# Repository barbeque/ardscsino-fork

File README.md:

## Current Status
Dirty ArdSCSIno II, V1 board works on at least one system using the BlueSCSI v1 USB firmware. Please refer to the table below for full testing.

| Platform          | Works?    | Comments |
|-------------------|-----------|----------|
| Macintosh LC | Yes | With termination power |

## Flashing
**Warning**: these instructions are a work in progress. Please report any hangups (that aren't related to crappy Blue Pills, see below) so we can fix this section.

I have used [the BlueSCSI Updater project](https://github.com/erichelgeson/BlueSCSI-Updater) to flash these, but you can also use the QMK Toolbox project which basically runs the same commands.

You will need an STLink-V2 programmer (eBay clones are fine) and at least four jumper wires. I recommend doing this before you solder the Blue Pill to the board.

 1. Wire up the STLink-V2, making sure to pay attention to where on the programmer each wire ends up.
 2. Set the BOOT0 jumper (_furthest_ from the Reset switch) to 1 and connect the STLink-V2 to your computer.
 3. Run the BlueSCSI Updater, and select option 2 to program a bare Blue Pill board. The STLink should flash and then state that things are all good.
 4. Do not hit Return yet!
 5. Unplug the STLink-V2 from both the Blue Pill and the computer. 
 6. Reset the BOOT0 jumper to 0. Set the BOOT1 jumper (_closest_ to the reset switch) to 1.
 7. Plug the Blue Pill into your computer through USB. Wait a couple seconds.
 8. Now you can hit Return and let the BlueSCSI Updater flash your Blue Pill.
 9. Unplug it, set the jumpers back to default, and enjoy your board.

For the boards without jumpers (i.e. the USB-C ones that I warn about lower down - go take a look) you can do the following steps instead:

 0. Do all the preceding steps from the regular Blue Pill.
 1. Hold the BOOT0 button on the Blue Pill while inserting the ST-Link into your computer. Keep holding it while you run the BlueSCSI Updater and write the bare firmware. Release the BOOT0 button and unplug it and the ST-Link once done.
 2. In stage two, plug the Blue Pill in via USB-C, start the firmware update process, and hit the nRST (reset) button on the top when the flasher is waiting for the device to appear. It should proceed.

## Bill of Materials (BOM)

| Position | Component              | Digi-Key part number | Comments                               |
|----------|------------------------|----------------------|----------------------------------------|
| C1 | 4.7µF through-hole capacitor | | |
| C2 | 0.1µF 0805 SMD ceramic capacitor | | |
| D1 | Optional activity LED, 3mm radial | | |
| J1 | 50-pin SCSI box header, male | 3M157291-ND | |
| J2 | 4-pin Berg floppy power, TE 171825-4 | A106197-ND | |
| J3 | micro SD card slot, Hirose DM3AT-SF-PEJM5 | HR1964CT-ND | |
| U2 | STM32 Blue Pill **C8T6** | | This should be sourced from AliExpress; see below for common problems. |
| R1 | 560Ω through-hole resistor | | |
| RN1, RN4 | 10-pin (9-way) bussed 220Ω resistor network | 4610X-1-221LF-ND | |
| RN2, RN3 | 10-pin (9-way) bussed 330Ω resistor network | 4610X-1-331LF-ND | |

## Common Blue Pill problems
Because the STM32 Blue Pill has been knocked off by a jillion different individuals, here are some of the problems I've encountered while trying to build these boards.

You might want to try the [Blue Pill Diagnostics project](https://mecrisp-stellaris-folkdoc.sourceforge.io/bluepill-diags-v1.640.html#diags-1-640). Again, it's a good idea to run this before you solder your microcontroller down. It really sucks to desolder it after! Ask me how I know.

### Surprise +5V pin
On many Blue Pills sold today, pin 40 is a "5V" pin. My board expects this pin to be ground. If you try to bring it up without modification, it will short the +5V power supply to ground and probably cause something unpleasant to happen.

The best thing to do here is to simply not solder this pin to the board: I do a 20-pin male header on one side and a 19-pin male header on the other side.

Please notice also that the LED pin on this board is changed from normal; BlueSCSI firmware will expect it at PC13 and this one is at PB2.

### Not enough flash
Make sure you are getting a STM32...C8T6 board. These have enough flash for the BlueSCSI firmware. Otherwise, you can get a mysterious `LIBUSB_ERROR_TIMEOUT` (C6T6) and nothing will work.

The Blue Pill Diagnostics should report that you have at least 64kB of regular flash and at least 64kB of "hidden" flash. A C6 has only 32kB.

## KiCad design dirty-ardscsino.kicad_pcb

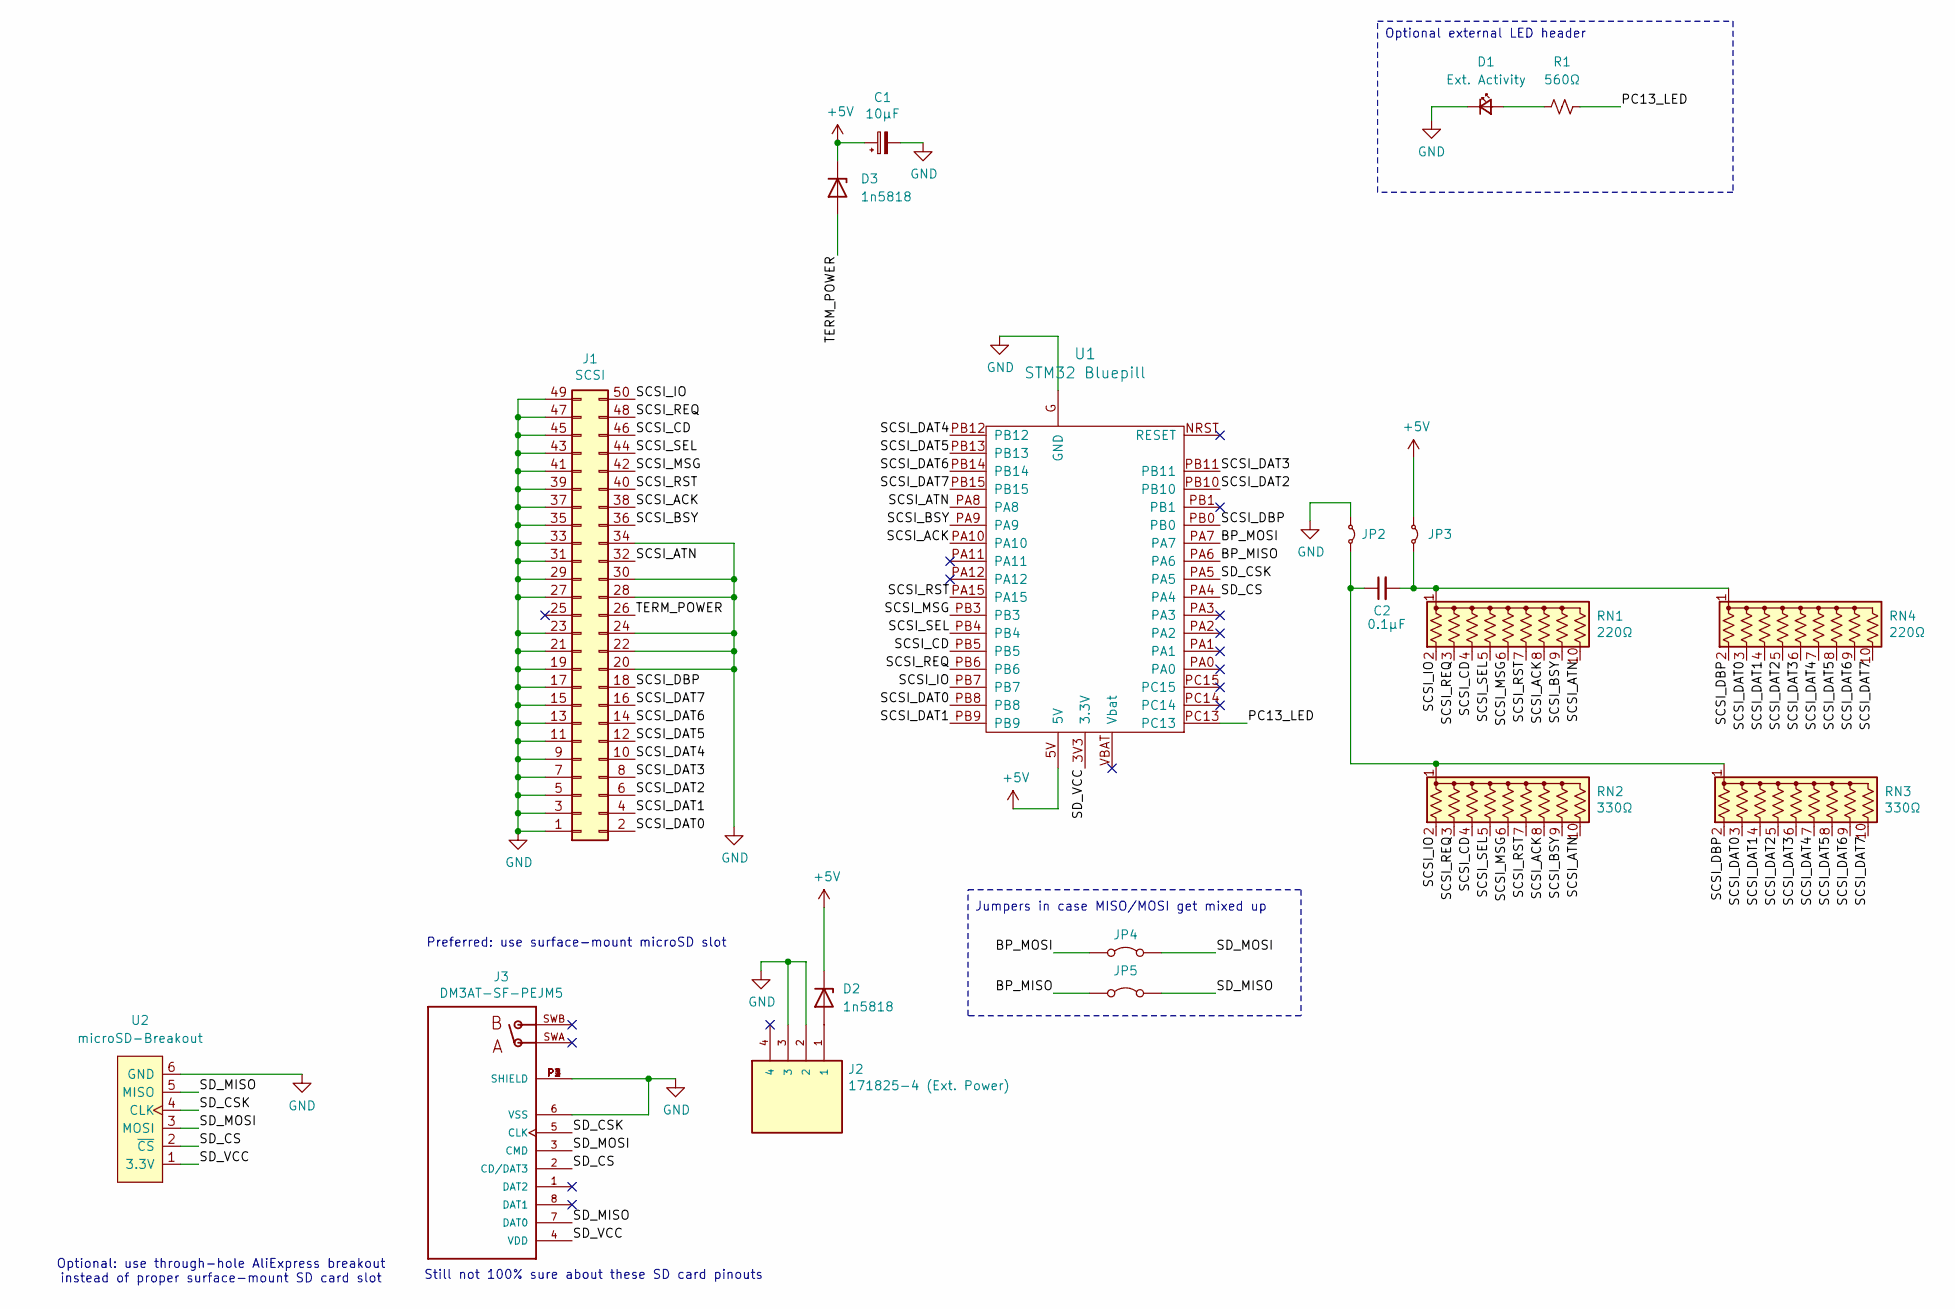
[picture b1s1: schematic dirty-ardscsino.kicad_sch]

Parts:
C1: 10µF; CP_Radial_D5.0mm_P2.00mm
C2: 0.1µF; C_0805_2012Metric_Pad1.18x1.45mm_HandSolder
D1: Ext. Activity; LED_D3.0mm
D2, D3: 1n5818; D_DO-41_SOD81_P7.62mm_Horizontal
J1: SCSI; PinHeader_2x25_P2.54mm_Horizontal; DigiKey 3M157291-ND
J2: 171825-4 (Ext. Power); TE_171825-4; DigiKey A106197-ND
J3: DM3AT-SF-PEJM5; HRS_DM3AT-SF-PEJM5; DigiKey HR1964CT-ND
JP2, JP3: Jumper_2_Small_Bridged; SolderJumper-2_P1.3mm_Bridged_RoundedPad1.0x1.5mm
JP4, JP5: Jumper_2_Bridged; SolderJumper-2_P1.3mm_Bridged_RoundedPad1.0x1.5mm
R1: 560Ω; R_Axial_DIN0207_L6.3mm_D2.5mm_P10.16mm_Horizontal
RN1, RN4: 220Ω; R_Array_SIP10; DigiKey 4610X-1-221LF-ND
RN2, RN3: 330Ω; R_Array_SIP10; DigiKey 4610X-1-331LF-ND
U1: STM32 Bluepill; blue_pill
U2: microSD-Breakout; microSD_AliExpress

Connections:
+5V: C1.1, D2.1 (K), D3.1 (K), JP3.1 (A), U1.5V
/BP_MISO: JP5.1 (A), U1.PA6
/BP_MOSI: JP4.1 (A), U1.PA7
/PC13_LED: R1.2, U1.PC13
/SCSI_ACK: J1.38, RN1.8 (R7), RN2.8 (R7), U1.PA10
/SCSI_ATN: J1.32, RN1.10 (R9), RN2.10 (R9), U1.PA8
/SCSI_BSY: J1.36, RN1.9 (R8), RN2.9 (R8), U1.PA9
/SCSI_CD: J1.46, RN1.4 (R3), RN2.4 (R3), U1.PB5
/SCSI_DAT0: J1.2, RN3.3 (R2), RN4.3 (R2), U1.PB8
/SCSI_DAT1: J1.4, RN3.4 (R3), RN4.4 (R3), U1.PB9
/SCSI_DAT2: J1.6, RN3.5 (R4), RN4.5 (R4), U1.PB10
/SCSI_DAT3: J1.8, RN3.6 (R5), RN4.6 (R5), U1.PB11
/SCSI_DAT4: J1.10, RN3.7 (R6), RN4.7 (R6), U1.PB12
/SCSI_DAT5: J1.12, RN3.8 (R7), RN4.8 (R7), U1.PB13
/SCSI_DAT6: J1.14, RN3.9 (R8), RN4.9 (R8), U1.PB14
/SCSI_DAT7: J1.16, RN3.10 (R9), RN4.10 (R9), U1.PB15
/SCSI_DBP: J1.18, RN3.2 (R1), RN4.2 (R1), U1.PB0
/SCSI_IO: J1.50, RN1.2 (R1), RN2.2 (R1), U1.PB7
/SCSI_MSG: J1.42, RN1.6 (R5), RN2.6 (R5), U1.PB3
/SCSI_REQ: J1.48, RN1.3 (R2), RN2.3 (R2), U1.PB6
/SCSI_RST: J1.40, RN1.7 (R6), RN2.7 (R6), U1.PA15
/SCSI_SEL: J1.44, RN1.5 (R4), RN2.5 (R4), U1.PB4
/SD_CS: J3.2 (CD/DAT3), U1.PA4, U2.2 (~CS)
/SD_CSK: J3.5 (CLK), U1.PA5, U2.4 (CLK)
/SD_MISO: J3.7 (DAT0), JP5.2 (B), U2.5 (MISO)
/SD_MOSI: J3.3 (CMD), JP4.2 (B), U2.3 (MOSI)
/SD_VCC: J3.4 (VDD), U1.3V3 (3.3V), U2.1 (3.3V)
/TERM_POWER: D3.2 (A), J1.26
GND: C1.2, D1.1 (K), J1.1, J1.3, J1.5, J1.7, J1.9, J1.11, J1.13, J1.15, J1.17, J1.19, J1.20, J1.21, J1.22, J1.23, J1.24, J1.27, J1.28, J1.29, J1.30, J1.31, J1.33, J1.34, J1.35, J1.37, J1.39, J1.41, J1.43, J1.45, J1.47, J1.49, J2.2, J2.3, J3.6 (VSS), J3.P1 (SHIELD), J3.P2 (SHIELD), J3.P3 (SHIELD), J3.P4 (SHIELD), JP2.1 (A), U1.G (GND), U2.6 (GND)
unnamed: D1.2 (A), R1.1
unnamed: D2.2 (A), J2.1
unnamed: C2.1, JP2.2 (B), RN2.1 (common), RN3.1 (common)
unnamed: C2.2, JP3.2 (B), RN1.1 (common), RN4.1 (common)

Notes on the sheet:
Preferred: use surface-mount microSD slot
Jumpers in case MISO/MOSI get mixed up
Optional: use through-hole AliExpress breakout instead of proper surface-mount SD card slot
Optional external LED header
Still not 100% sure about these SD card pinouts

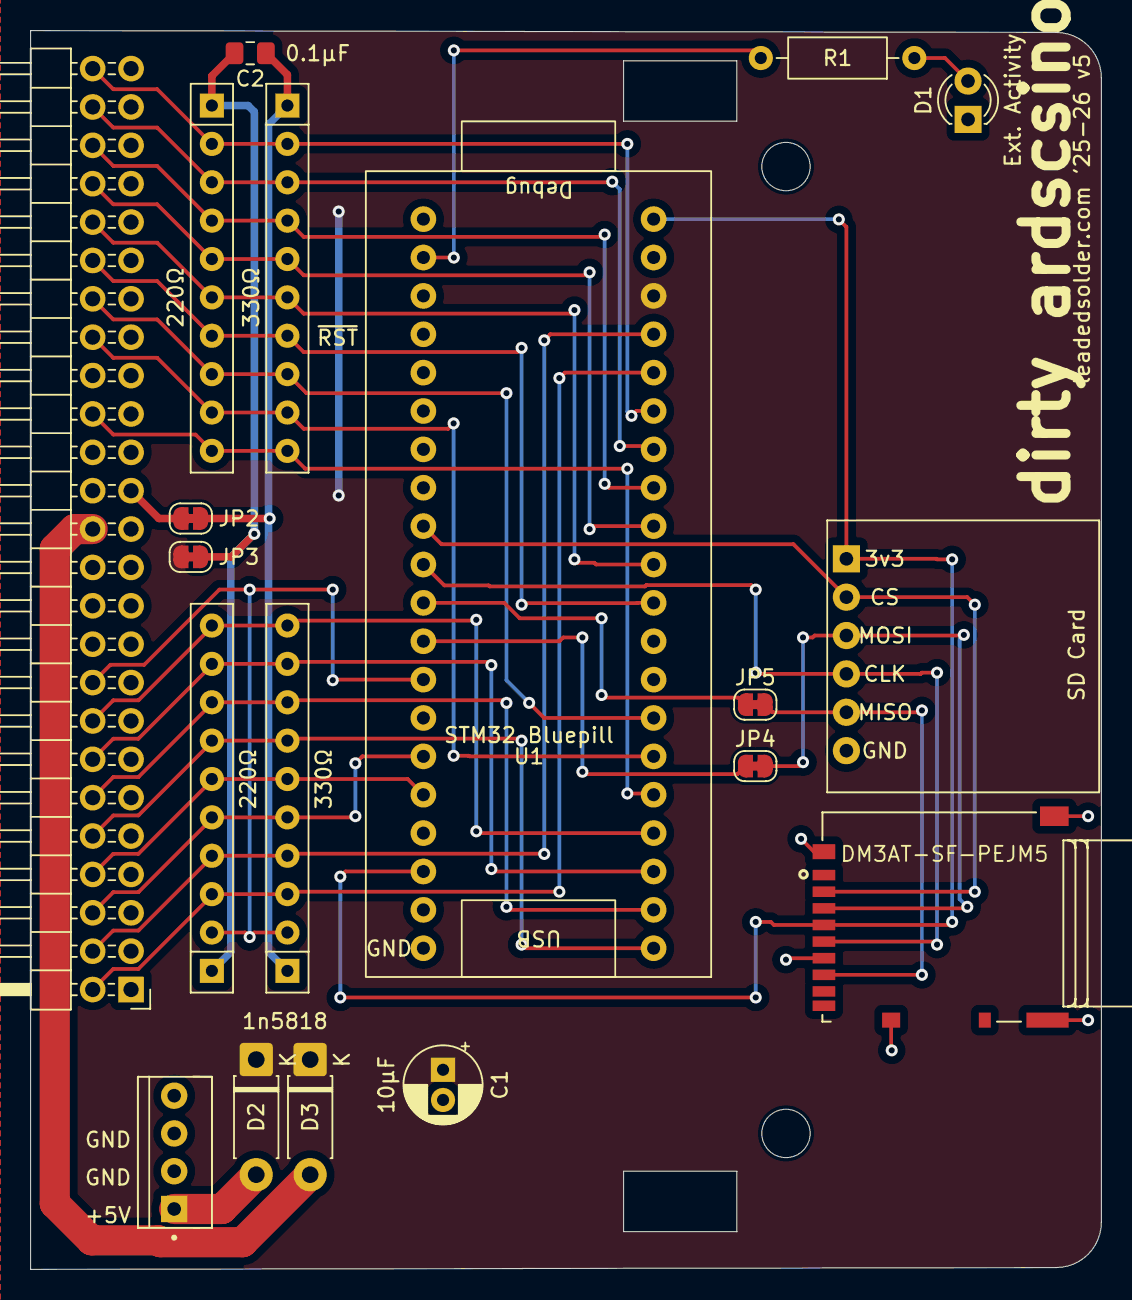
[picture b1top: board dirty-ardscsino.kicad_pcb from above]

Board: 2 copper layers, 70.9 x 82.0 mm, 19 parts (0 on the bottom side), 33 nets.

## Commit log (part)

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2021-02-18 Diagrams and footprints
2021-02-18 Termination resistors
2021-02-19 Layout except for SD card
2021-02-19 Add OSHW
2021-02-19 Passed DRC
2021-02-19 Gerber v0.1 test
2021-02-19 Clean up notes
2021-02-19 Add shore power switch and decoupling
2021-02-19 Clean up silks
2021-02-19 Add a smaller bypass to the termination grid as well
2021-02-19 Missed this before
2021-02-19 Move the cap so I don't hit it with USB
2021-02-23 Add 180-degree floppy power conn
2021-02-23 Add DigiKey BOM tags
2021-02-23 Fix the footprint tab AGAIN
2023-05-12 Good looking board layout
2024-04-09 KiCad upgrade
2024-04-09 Flip power labels so you can read them
2024-04-09 Improve assembly labeling
2025-06-09 Dirty ArdSCSIno 2 v1 sent to fab
2025-06-09 Re-add mounting holes (oops)
2025-06-09 Notes for later
2025-06-22 Label the term. power pin
2025-06-24 Schem cleanup
2025-06-24 Longer pads for SD card reader
2025-06-24 Better labels
2025-06-25 Moved power connector, bigger pads, added silkscreen for debug header
2025-06-25 Dunno
2025-07-22 junk pills
2025-07-22 Add warning text to PCB
2025-07-23 Reduce USB interference with jumper
2025-07-23 BlueSCSI led pin
2025-07-23 Make microSD breakout more friendly
2025-07-27 Readme ramble
2025-08-01 Remove MISO/MOSI poke-a-yoke; install termination-killing jumpers
2025-08-02 Optional activity LED
2025-08-02 Prepare version 2 for manufacture
2025-08-02 Add LCSC part for the SD card
2025-08-04 Add tag to show where RST is, in case this makes it work
2026-05-13 Update TODO
2026-05-13 Fix potential bug, BOM
2026-05-13 More updates
2026-05-13 Stricter claims on BOM
